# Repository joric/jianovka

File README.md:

# Jianovka

Bezkont Klavesnice Zbrojovka hardware-based keyboard with Jian-based layout

Originally from https://nest.pijul.com/sunflower/jianovka

## Building

Copy firmware folder into qmk_firmware/keyboards/jianovka, run `make jianovka:default`.

## Pictures

## References

* https://nest.pijul.com/sunflower/jianovka
* https://www.flickr.com/photos/triplehaata/albums/72157661916775494/
* https://www.bucek.name/pdf/mh3sd2,mh3ss2.pdf

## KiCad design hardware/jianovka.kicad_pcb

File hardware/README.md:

# Jianovka

Jianovka is a chorded keyboard that looks similar to Jian or Corne keyboard, but uses chords instead of layers. Columnar stagger and thumb cluster are copied from Jian keyboard, but far-far-away pinky key removed. So Jianovka looks more like Jian, but has 42 keys like Corne.

This keyboard is designed to be made with Hall effect switches and keys from vintage Zbrojovka 262.3 keyboard, Teensy 2.0 microcontroller and QMK firmware.

Keyboard Maintainer: [Dmitry Nikolaev](https://nest.pijul.com/sunflower)

Files in this repository, except those made not by me, are in public domain.

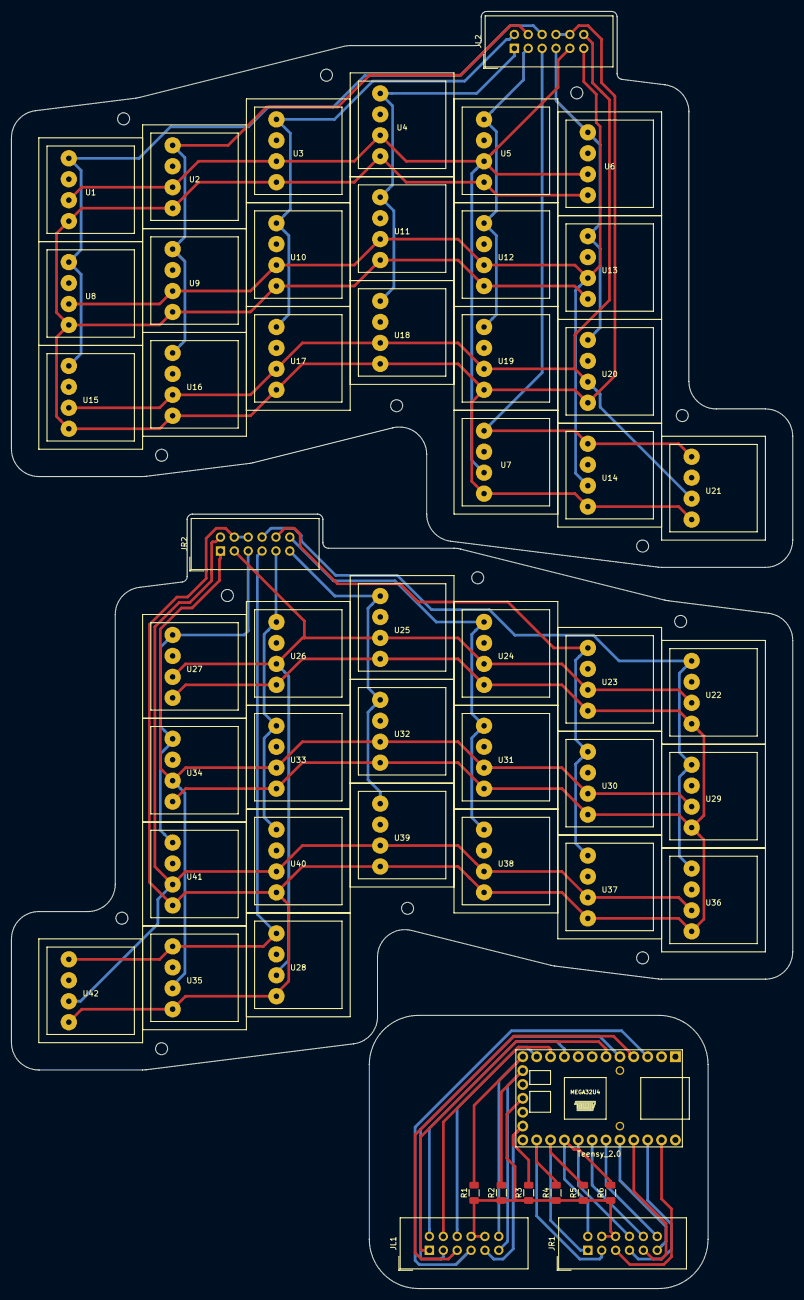
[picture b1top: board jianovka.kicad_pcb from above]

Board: 2 copper layers, 143.0 x 233.8 mm, 53 parts (0 on the bottom side), 43 nets.

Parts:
JL1, JL2: Conn_02x06_Top_Bottom; IDC-Header_2x06_P2.54mm_Vertical
JR1, JR2: Conn_02x06_Top_Bottom; IDC-Header_2x06_P2.54mm_Vertical
R1, R2, R3, R4, R5, R6: R; R_1206_3216Metric
Teensy_2.0: Teensy2.0_(C); Teensy2.0
U1, U2, U3, U4, U5, U6, U7, U8, U9, U10, U11, U12, U13, U14, U15, U16, U17, U18, U19, U20, U21, U22, U23, U24, U25, U26, U27, U28, U29, U30, U31, U32, U33, U34, U35, U36, U37, U38, U39, U40, U41, U42: MH3SS2

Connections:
unnamed: JL1.1, Teensy_2.0.6
unnamed: JL1.2, Teensy_2.0.9
unnamed: JL1.3, Teensy_2.0.5
unnamed: JL1.4, Teensy_2.0.10
unnamed: JL1.5, Teensy_2.0.4
unnamed: JL1.6, Teensy_2.0.11
unnamed: JL1.7, Teensy_2.0.3
unnamed: JL1.9, R3.2, Teensy_2.0.17
unnamed: JL1.8, JL1.10, JR1.4, JR1.6, R1.1, R2.1, R3.1, R4.1, R5.1, R6.1, Teensy_2.0.15
unnamed: JL1.11, R2.2, Teensy_2.0.13
unnamed: JL1.12, R1.2, Teensy_2.0.12
unnamed: JL2.1, U4.4, U11.4, U18.4
unnamed: JL2.2, U3.4, U10.4, U17.4
unnamed: JL2.3, U5.4, U12.4, U19.4
unnamed: JL2.4, U2.4, U9.4, U16.4
unnamed: JL2.5, U7.4, U14.4, U21.4
unnamed: JL2.6, U1.4, U8.4, U15.4
unnamed: JL2.7, U6.4, U13.4, U20.4
unnamed: JL2.9, U1.2, U2.2, U3.2, U4.2, U5.2, U6.2, U7.2
unnamed: JL2.8, JL2.10, U1.1, U2.1, U3.1, U4.1, U5.1, U6.1, U7.1, U8.1, U9.1, U10.1, U11.1, U12.1, U13.1, U14.1, U15.1, U16.1, U17.1, U18.1, U19.1, U20.1, U21.1
unnamed: JL2.11, U8.2, U9.2, U10.2, U11.2, U12.2, U13.2, U14.2
unnamed: JL2.12, U15.2, U16.2, U17.2, U18.2, U19.2, U20.2, U21.2
unnamed: JR1.1, R5.2, Teensy_2.0.20
unnamed: JR1.2, R6.2, Teensy_2.0.21
unnamed: JR1.3, R4.2, Teensy_2.0.19
unnamed: JR1.5, Teensy_2.0.28
unnamed: JR1.7, Teensy_2.0.27
unnamed: JR1.8, Teensy_2.0.22
unnamed: JR1.9, Teensy_2.0.26
unnamed: JR1.10, Teensy_2.0.23
unnamed: JR1.11, Teensy_2.0.25
unnamed: JR1.12, Teensy_2.0.24
unnamed: JR2.1, U29.2, U30.2, U31.2, U32.2, U33.2, U34.2, U35.2
unnamed: JR2.2, U36.2, U37.2, U38.2, U39.2, U40.2, U41.2, U42.2
unnamed: JR2.3, U22.2, U23.2, U24.2, U25.2, U26.2, U27.2, U28.2
unnamed: JR2.4, JR2.6, U22.1, U23.1, U24.1, U25.1, U26.1, U27.1, U28.1, U29.1, U30.1, U31.1, U32.1, U33.1, U34.1, U35.1, U36.1, U37.1, U38.1, U39.1, U40.1, U41.1, U42.1
unnamed: JR2.5, U27.4, U34.4, U41.4
unnamed: JR2.7, U28.4, U35.4, U42.4
unnamed: JR2.8, U22.4, U29.4, U36.4
unnamed: JR2.9, U26.4, U33.4, U40.4
unnamed: JR2.10, U23.4, U30.4, U37.4
unnamed: JR2.11, U25.4, U32.4, U39.4
unnamed: JR2.12, U24.4, U31.4, U38.4
